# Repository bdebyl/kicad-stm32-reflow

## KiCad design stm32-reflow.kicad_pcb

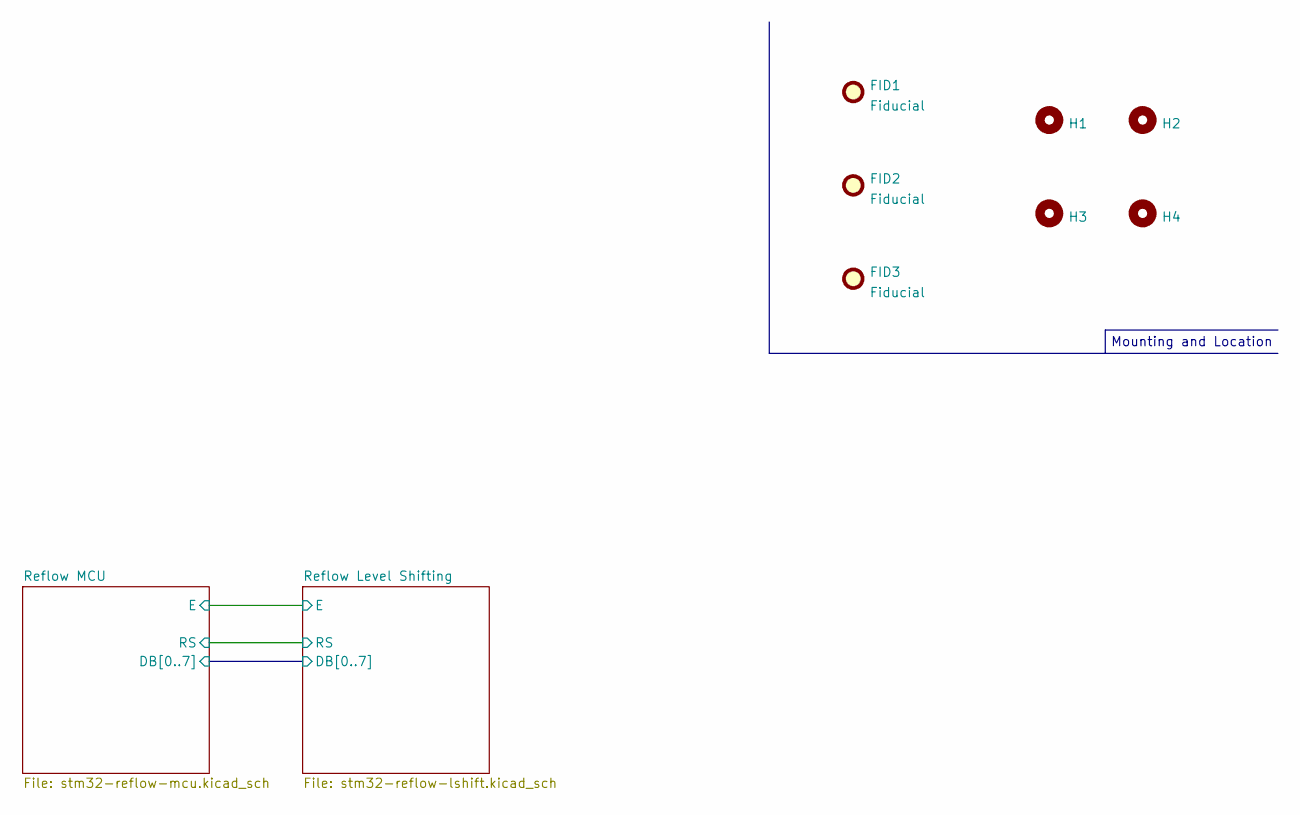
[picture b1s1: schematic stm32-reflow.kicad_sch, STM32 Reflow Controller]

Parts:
FID1, FID2, FID3: Fiducial; Fiducial_0.75mm_Mask2.25mm
H1, H2, H3, H4: MountingHole; MountingHole_2.7mm_M2.5_Pad_Via

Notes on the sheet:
Mounting and Location

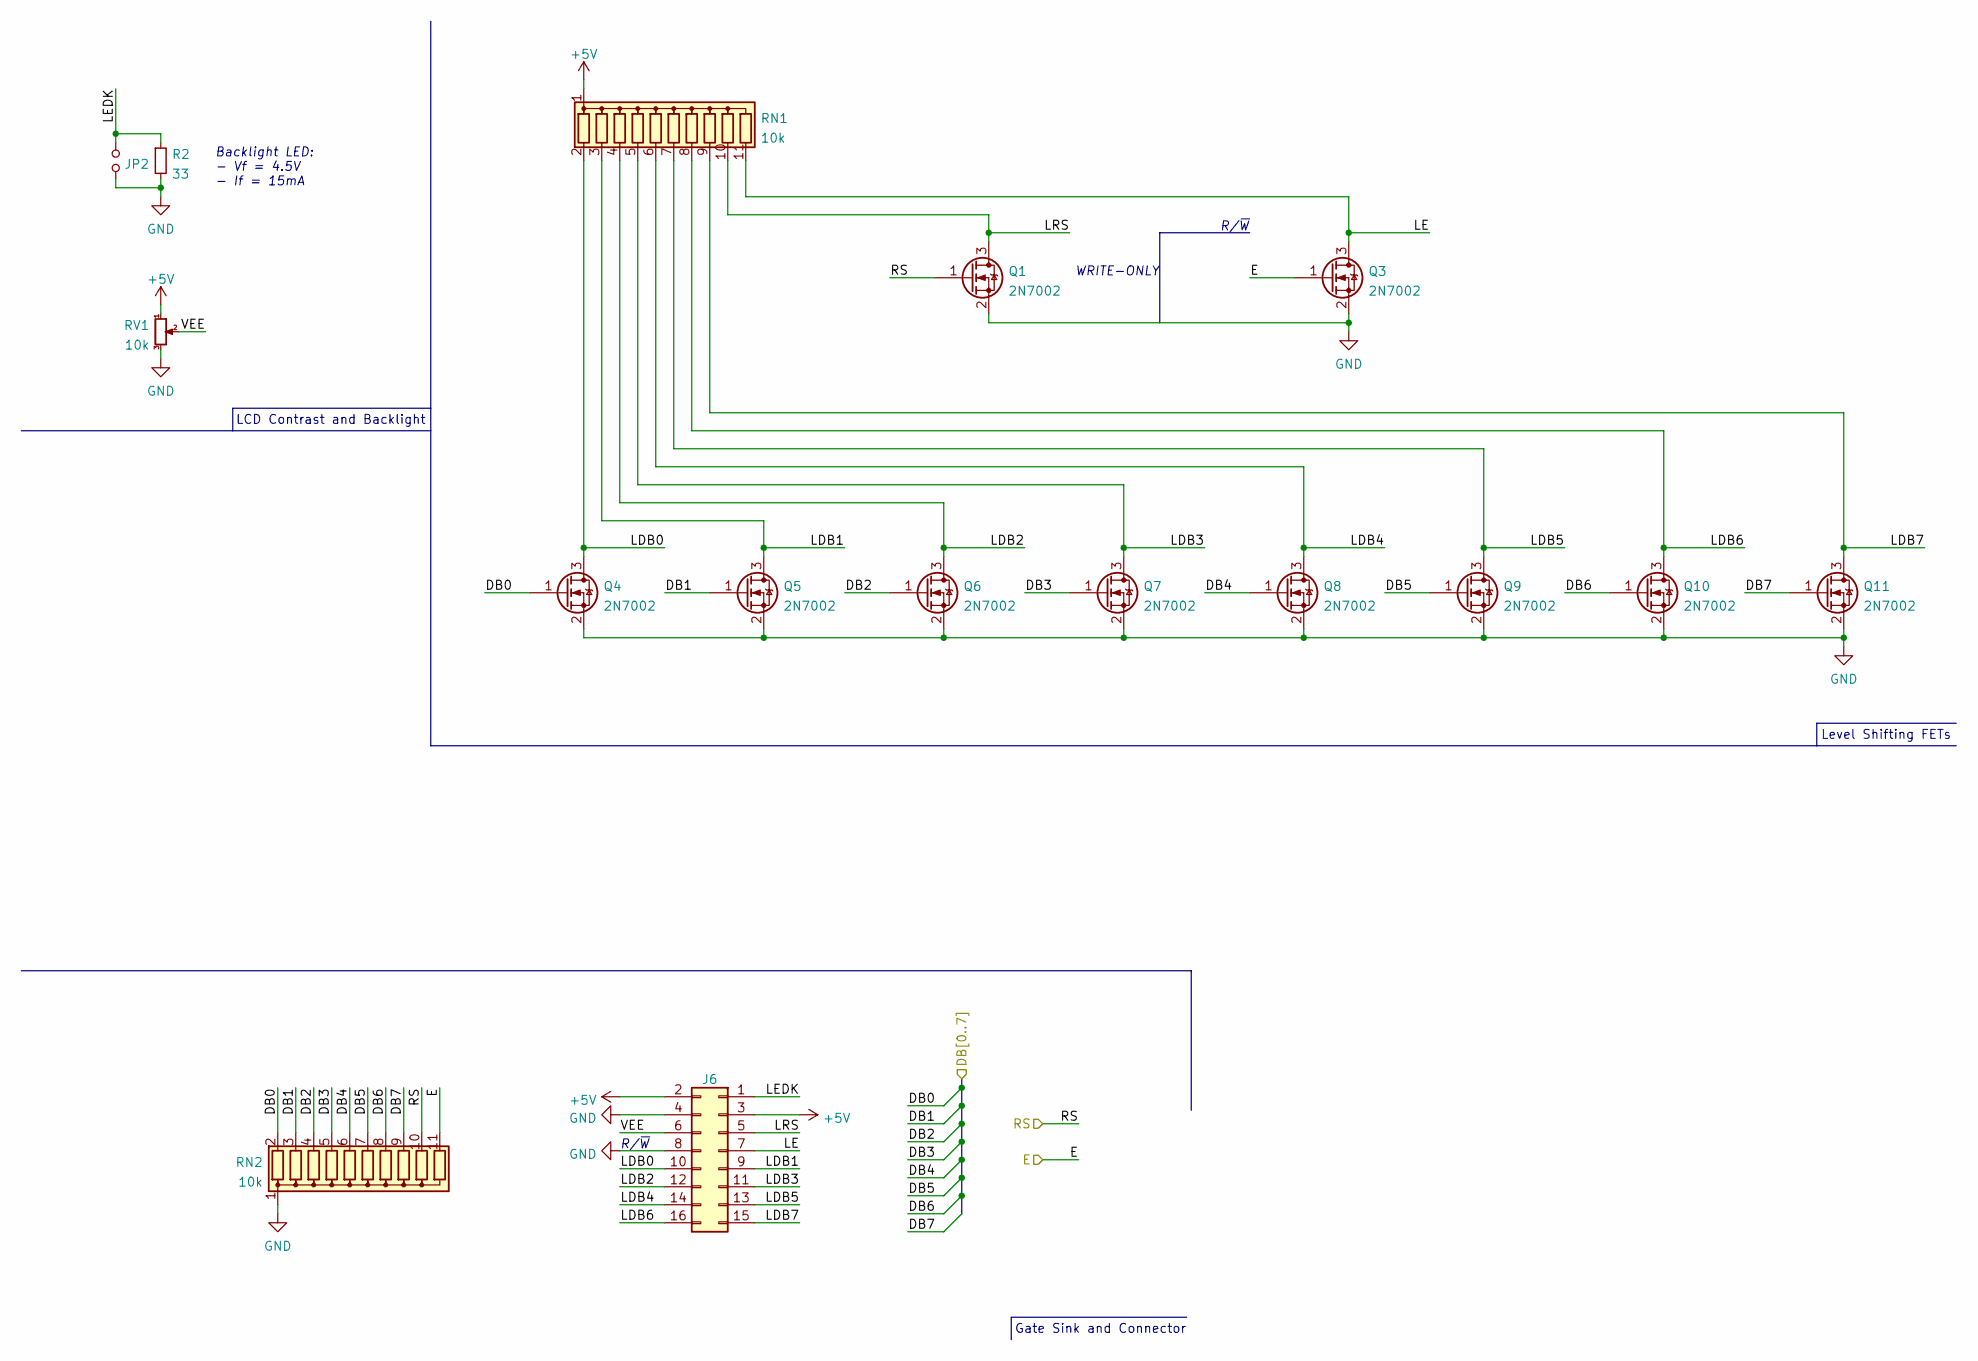
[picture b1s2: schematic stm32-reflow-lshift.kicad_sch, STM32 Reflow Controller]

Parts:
J6: Conn_02x08_Odd_Even; IDC-Header_2x08_P2.54mm_Vertical; DigiKey Part # S9171-ND
JP2: Jumper_NO_Small; SolderJumper-2_P1.3mm_Open_TrianglePad1.0x1.5mm
Q1, Q3, Q4, Q5, Q6, Q7, Q8, Q9, Q10, Q11: 2N7002; SOT-23; DigiKey Part # 1727-8642-1-ND
R2: 33; R_0805_2012Metric; DigiKey Part # RMCF0805JT33R0CT-ND
RN1, RN2: 10k; R_Array_SIP11; DigiKey Part # 4611X-101-103LF-ND
RV1: 10k; Potentiometer_Bourns_3314G_Vertical; DigiKey Part # ST4ETB103CT-ND

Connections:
+5V: J6.2, J6.3, RN1.1 (common), RV1.1; also elsewhere on the board
/Reflow Level Shifting/DB0: Q4.1 (G), RN2.2 (R1); also elsewhere on the board
/Reflow Level Shifting/DB1: Q5.1 (G), RN2.3 (R2); also elsewhere on the board
/Reflow Level Shifting/DB2: Q6.1 (G), RN2.4 (R3); also elsewhere on the board
/Reflow Level Shifting/DB3: Q7.1 (G), RN2.5 (R4); also elsewhere on the board
/Reflow Level Shifting/DB4: Q8.1 (G), RN2.6 (R5); also elsewhere on the board
/Reflow Level Shifting/DB5: Q9.1 (G), RN2.7 (R6); also elsewhere on the board
/Reflow Level Shifting/DB6: Q10.1 (G), RN2.8 (R7); also elsewhere on the board
/Reflow Level Shifting/DB7: Q11.1 (G), RN2.9 (R8); also elsewhere on the board
/Reflow Level Shifting/E: Q3.1 (G), RN2.11 (R10); also elsewhere on the board
/Reflow Level Shifting/LDB0: J6.10, Q4.3 (D), RN1.2 (R1)
/Reflow Level Shifting/LDB1: J6.9, Q5.3 (D), RN1.3 (R2)
/Reflow Level Shifting/LDB2: J6.12, Q6.3 (D), RN1.4 (R3)
/Reflow Level Shifting/LDB3: J6.11, Q7.3 (D), RN1.5 (R4)
/Reflow Level Shifting/LDB4: J6.14, Q8.3 (D), RN1.6 (R5)
/Reflow Level Shifting/LDB5: J6.13, Q9.3 (D), RN1.7 (R6)
/Reflow Level Shifting/LDB6: J6.16, Q10.3 (D), RN1.8 (R7)
/Reflow Level Shifting/LDB7: J6.15, Q11.3 (D), RN1.9 (R8)
/Reflow Level Shifting/LE: J6.7, Q3.3 (D), RN1.11 (R10)
/Reflow Level Shifting/LEDK: J6.1, JP2.2, R2.1
/Reflow Level Shifting/LRS: J6.5, Q1.3 (D), RN1.10 (R9)
/Reflow Level Shifting/RS: Q1.1 (G), RN2.10 (R9); also elsewhere on the board
/Reflow Level Shifting/VEE: J6.6, RV1.2
GND: J6.4, J6.8, JP2.1, Q1.2 (S), Q3.2 (S), Q4.2 (S), Q5.2 (S), Q6.2 (S), Q7.2 (S), Q8.2 (S), Q9.2 (S), Q10.2 (S), Q11.2 (S), R2.2, RN2.1 (common), RV1.3; also elsewhere on the board

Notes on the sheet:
Backlight LED: - Vf = 4.5V - If = 15mA
LCD Contrast and Backlight
R/~{W}
WRITE-ONLY
Gate Sink and Connector
Level Shifting FETs

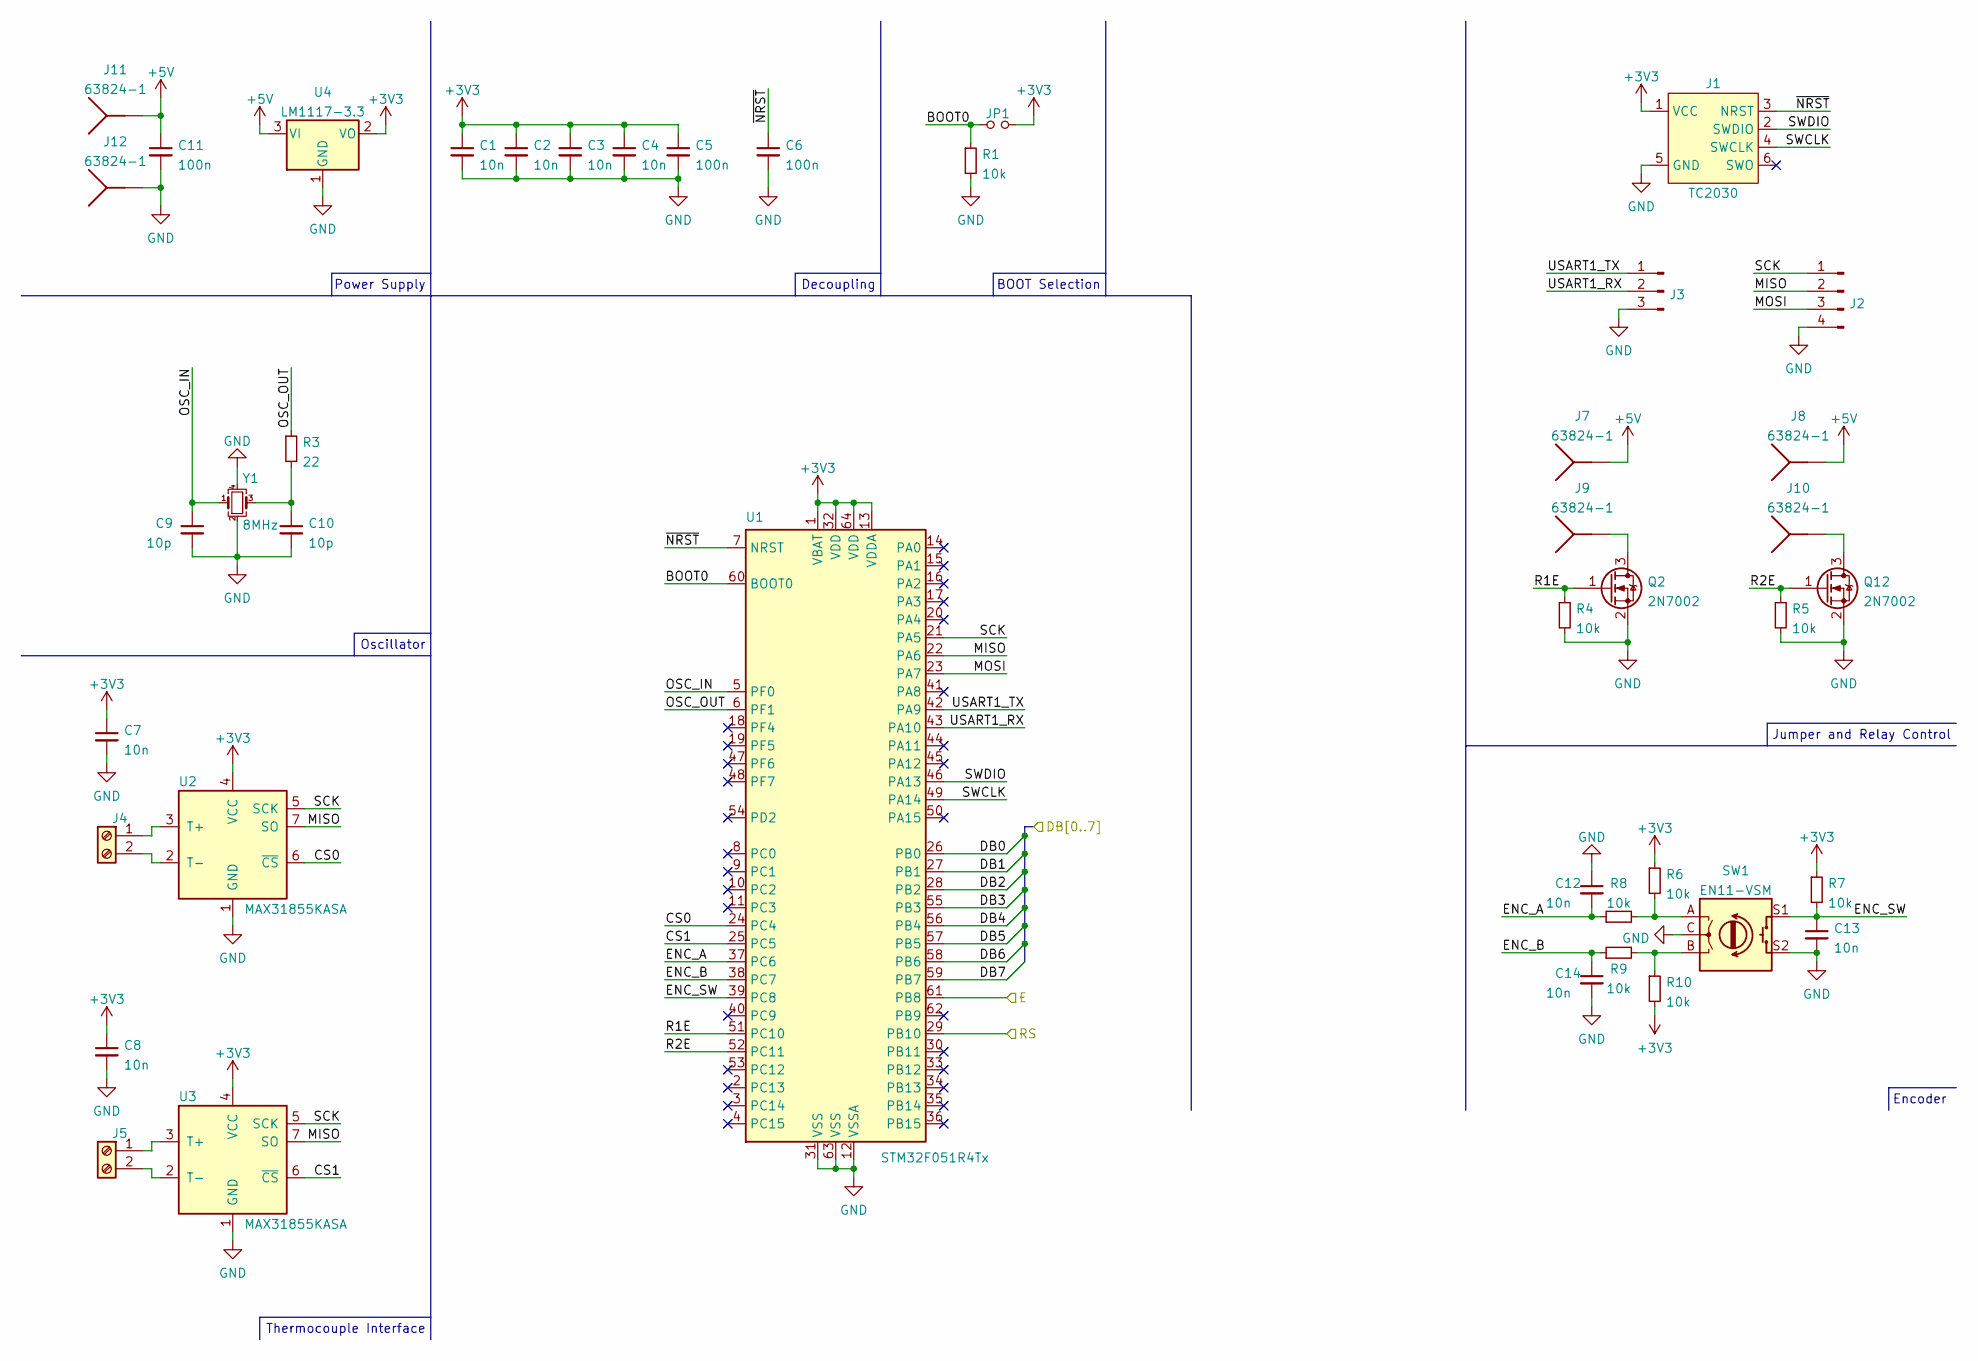
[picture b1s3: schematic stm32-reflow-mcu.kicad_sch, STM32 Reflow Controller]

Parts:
C1, C2, C3, C4, C7, C8, C12, C13, C14: 10n; C_0603_1608Metric; DigiKey Part # 732-8007-2-ND
C5, C6, C11: 100n; C_0805_2012Metric; DigiKey Part # 732-7760-2-ND
C9, C10: 10p; C_0603_1608Metric; DigiKey Part # 732-7760-2-ND
J1: TC2030; TC2030-IDC-NL
J2: Conn_01x04_Male; PinHeader_1x04_P2.54mm_Vertical
J3: Conn_01x03_Male; PinHeader_1x03_P2.54mm_Vertical
J4, J5: Screw_Terminal_01x02; TerminalBlock_TE_282834-2_1x02_P2.54mm_Horizontal; DigiKey Part # ED10561-ND
J7, J8, J9, J10, J11, J12: 63824-1; CONN_63824-1; DigiKey Part # A29938CT-ND
JP1: Jumper_NO_Small; SolderJumper-2_P1.3mm_Open_Pad1.0x1.5mm
Q2, Q12: 2N7002; SOT-23; DigiKey Part # 1727-8642-1-ND
R1, R4, R5, R6, R7, R8, R9, R10: 10k; R_0603_1608Metric; DigiKey Part # RMCF0603JT10K0TR-ND
R3: 22; R_0603_1608Metric; DigiKey Part # CR0603-JW-220ELFTR-ND
SW1: EN11-VSM; EN11-VSM1AF20; DigiKey Part # 987-1192-ND
U1: STM32F051R4Tx; LQFP-64_10x10mm_P0.5mm
U2, U3: MAX31855KASA; SOIC-8_3.9x4.9mm_P1.27mm
U4: LM1117-3.3; SOT-223-3_TabPin2; DigiKey Part # 497-3455-2-ND
Y1: 8MHz; Crystal_SMD_5032-4Pin_5.0x3.2mm; DigiKey Part # 1923-LFXTAL061627REELCT-ND

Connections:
+3V3: C1.1, C2.1, C3.1, C4.1, C5.1, C7.1, C8.1, J1.1 (VCC), JP1.2, R6.1, R7.1, R10.2, U1.1 (VBAT), U1.13 (VDDA), U1.32 (VDD), U1.64 (VDD), U2.4 (VCC), U3.4 (VCC), U4.2 (VO)
+5V: C11.1, J7.1, J7.2, J8.1, J8.2, J11.1, J11.2, U4.3 (VI); also elsewhere on the board
/Reflow Level Shifting/DB0: U1.26 (PB0); also elsewhere on the board
/Reflow Level Shifting/DB1: U1.27 (PB1); also elsewhere on the board
/Reflow Level Shifting/DB2: U1.28 (PB2); also elsewhere on the board
/Reflow Level Shifting/DB3: U1.55 (PB3); also elsewhere on the board
/Reflow Level Shifting/DB4: U1.56 (PB4); also elsewhere on the board
/Reflow Level Shifting/DB5: U1.57 (PB5); also elsewhere on the board
/Reflow Level Shifting/DB6: U1.58 (PB6); also elsewhere on the board
/Reflow Level Shifting/DB7: U1.59 (PB7); also elsewhere on the board
/Reflow Level Shifting/E: U1.61 (PB8); also elsewhere on the board
/Reflow Level Shifting/RS: U1.29 (PB10); also elsewhere on the board
/Reflow MCU/BOOT0: JP1.1, R1.1, U1.60 (BOOT0)
/Reflow MCU/CS0: U1.24 (PC4), U2.6 (~CS)
/Reflow MCU/CS1: U1.25 (PC5), U3.6 (~CS)
/Reflow MCU/ENC_A: C12.2, R8.1, U1.37 (PC6)
/Reflow MCU/ENC_B: C14.1, R9.1, U1.38 (PC7)
/Reflow MCU/ENC_SW: C13.1, R7.2, SW1.S1, U1.39 (PC8)
/Reflow MCU/MISO: J2.2, U1.22 (PA6), U2.7 (SO), U3.7 (SO)
/Reflow MCU/MOSI: J2.3, U1.23 (PA7)
/Reflow MCU/OSC_IN: C9.1, U1.5 (PF0), Y1.1
/Reflow MCU/OSC_OUT: R3.1, U1.6 (PF1)
/Reflow MCU/R1E: Q2.1 (G), R4.1, U1.51 (PC10)
/Reflow MCU/R2E: Q12.1 (G), R5.1, U1.52 (PC11)
/Reflow MCU/SCK: J2.1, U1.21 (PA5), U2.5 (SCK), U3.5 (SCK)
/Reflow MCU/SWCLK: J1.4 (SWCLK), U1.49 (PA14)
/Reflow MCU/SWDIO: J1.2 (SWDIO), U1.46 (PA13)
/Reflow MCU/USART1_RX: J3.2, U1.43 (PA10)
/Reflow MCU/USART1_TX: J3.1, U1.42 (PA9)
/Reflow MCU/~NRST: C6.1, J1.3 (NRST), U1.7 (NRST)
GND: C1.2, C2.2, C3.2, C4.2, C5.2, C6.2, C7.2, C8.2, C9.2, C10.2, C11.2, C12.1, C13.2, C14.2, J1.5 (GND), J2.4, J3.3, J12.1, J12.2, Q2.2 (S), Q12.2 (S), R1.2, R4.2, R5.2, SW1.C, SW1.S2, U1.12 (VSSA), U1.31 (VSS), U1.63 (VSS), U2.1 (GND), U3.1 (GND), U4.1 (GND), Y1.2, Y1.4; also elsewhere on the board
unnamed: C10.1, R3.2, Y1.3
unnamed: J4.1, U2.3 (T+)
unnamed: J4.2, U2.2 (T-)
unnamed: J5.1, U3.3 (T+)
unnamed: J5.2, U3.2 (T-)
unnamed: J9.1, J9.2, Q2.3 (D)
unnamed: J10.1, J10.2, Q12.3 (D)
unnamed: R6.2, R8.2, SW1.A
unnamed: R9.2, R10.1, SW1.B

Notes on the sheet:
Power Supply
Oscillator
Thermocouple Interface
Decoupling
BOOT Selection
Encoder
Jumper and Relay Control

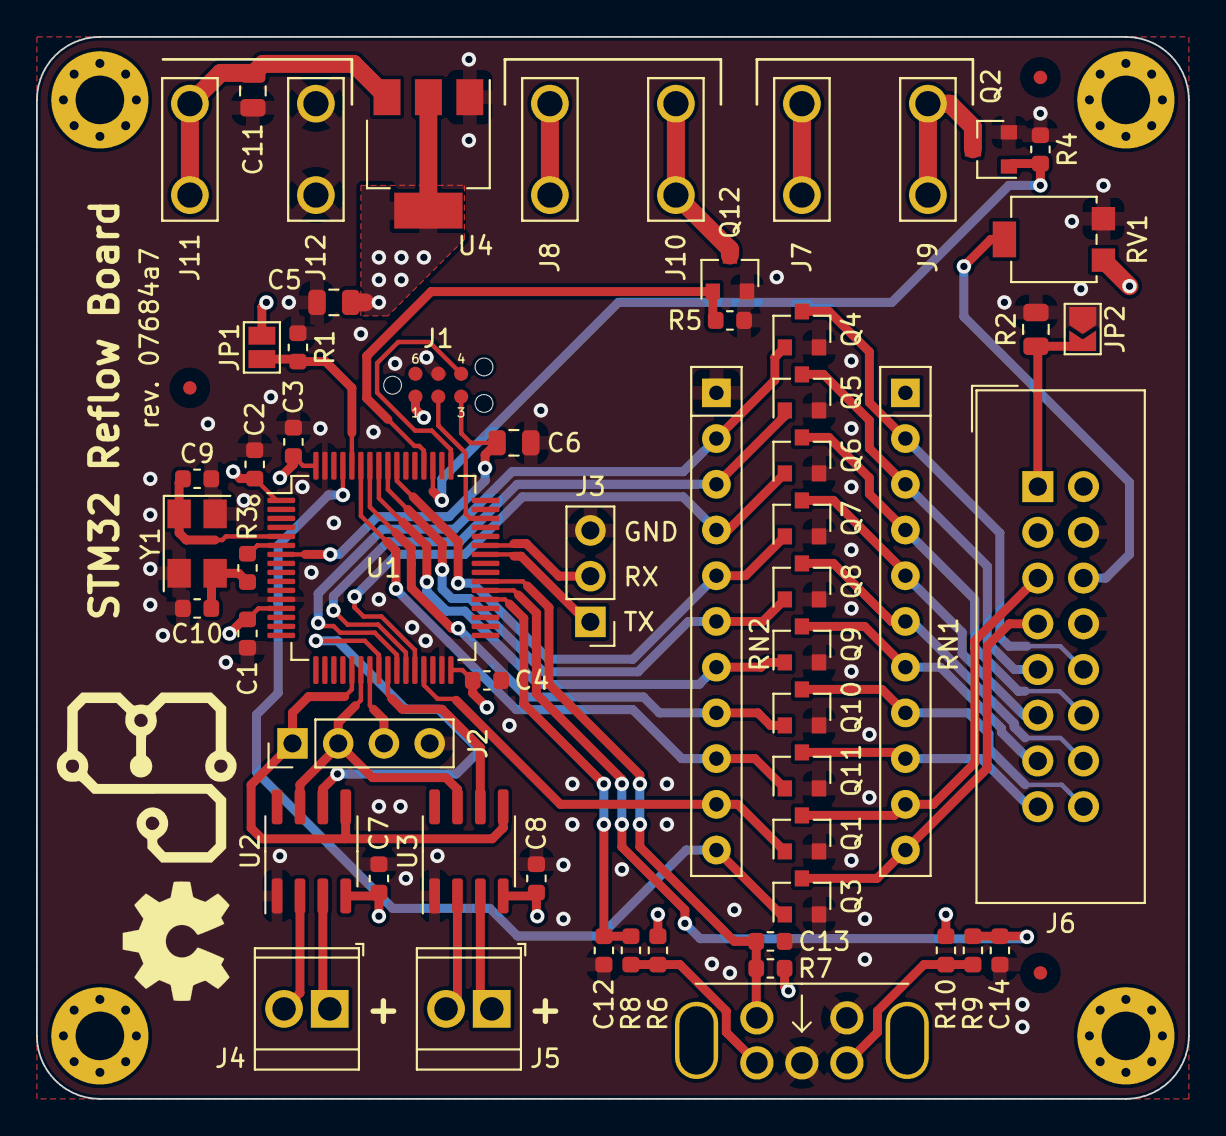
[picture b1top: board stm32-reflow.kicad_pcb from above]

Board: 4 copper layers, 64.0 x 59.0 mm, 66 parts (0 on the bottom side), 52 nets.

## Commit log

2021-11-26 initial routing, added power supply source
2021-11-26 finalized routing and circuit schematic (so far)
2021-11-26 fixed orientation of the LCD IDC connector
2021-11-26 ERC and DRC fixes
2021-11-26 added additional silkscreening
2021-11-26 downsized resistor network to 10
2021-11-26 consolidated schematics for clarity, labeling and organization
2021-11-26 added missign Oscillator schematic label
2021-11-26 fixed labeling of R1E & R2E
2021-11-26 moved silkscreening around, added labels
2021-11-26 added encoder interface
2021-11-26 organized schematic more, fixed net naming of rw
2021-11-29 finalized design for production
2021-11-29 added revision label, finalized for fabrication
2021-12-16 updated bom to reflect non-backordered parts
2022-01-18 updated board for proper kicad6.0 compati
